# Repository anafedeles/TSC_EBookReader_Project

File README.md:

# TSC_EBookReader_Project

## 
Proiectul **EOpenBook** este o platformă portabilă cu afișaj E-Paper, construită în jurul microcontrollerului ESP32-C6, cu scopul de a oferi o interfață de citire eficientă energetic și complet conectată. Include funcționalități precum:

- Afișare E-Paper cu consum redus
- Stocare locală pe memorie NOR și card microSD
- Monitorizare baterie și încărcare
- Ceas în timp real (RTC)
- Senzor de mediu cu detecție VOC
- Protecții ESD și rutare optimizată

## Diagramă bloc cu toate componentele proiectului

## Listă de materiale (BOM)

| Componentă             | Link pentru achizitionare                                                                                             | Link Datasheet                                                                                                      |
|------------------------|----------------------------------------------------------------------------------------------------------------|---------------------------------------------------------------------------------------------------------------------|
| 112A-TAAR-R03 ATTEND   | https://store.comet.srl.ro/Catalogue/Product/43497/                                                            | https://www.snapeda.com/parts/112A-TAAR-R03/Attend/datasheet/                                                     |
| BD5229G-TR             | https://www.digikey.com/en/products/detail/rohm-semiconductor/BD5229G-TR/3663792                             | https://fscdn.rohm.com/en/products/databook/datasheet/ic/power/voltage_detector/bd52xxg-e.pdf                      |
| ESP32 WROVER BME680 Sensor                 | https://store.comet.srl.ro/Catalogue/Product/50164/             | https://www.bosch-sensortec.com/media/boschsensortec/downloads/datasheets/bst-bme680-ds001.pdf                                                  |
| LED CHG_LED                | https://ro.mouser.com/ProductDetail/Kingbright/KP-1608SURCK?qs=2JU0tDl2GZ3FuyEWfBV1%2Fg==                     | https://www.snapeda.com/parts/KP-1608SURCK/Kingbright/datasheet/                                                  |
| Condensator C0402      | https://ro.mouser.com/c/passive-components/capacitors/ceramic-capacitors/?q=CC0402                           | https://componentsearchengine.com/Datasheets/2/CC0402MRX5R5BB106.pdf                                               |
| Condensator Tant  | https://ro.mouser.com/ProductDetail/KYOCERA-AVX/TAJW107M010RNJ?qs=Wtp%252Bf%2FAeVqIH8v1VxV%252B1Rg%3D%3D        | https://ro.mouser.com/datasheet/2/40/TAJ-3165264.pdf                                                               |
|Q1 DMG2305UX-7            | https://www.digikey.com/en/products/detail/diodes-incorporated/DMG2305UX-7/4340666                           | https://www.diodes.com/assets/Datasheets/DMG2305UX.pdf                                                             |
| RTC MODULE DS3231SN#              | https://www.snapeda.com/parts/DS3231SN%23/Analog+Devices/view-part/?ref=eda | https://www.snapeda.com/parts/DS3231SN%23/Analog%20Devices/datasheet/                                                          |
| ESP32 C6 WROOM-1-N8    | https://ro.mouser.com/ProductDetail/Espressif-Systems/ESP32-C6-WROOM-1-N8?qs=8Wlm6%252BaMh8ST02Gmwp74cw%3D%3D | https://www.snapeda.com/parts/ESP32-C6-WROOM-1-N8/Espressif%20Systems/datasheet/             |
| FH34SRJ-24S-0.5SH(99)  | https://ro.mouser.com/ProductDetail/Hirose-Connector/FH34SRJ-24S-0.5SH99?qs=vcbW%252B4%252BSTIpKBl5ap9J8Fw%3D%3D | https://www.snapeda.com/parts/FH34SRJ-24S-0.5SH(99)/Hirose%20Connector/datasheet/           |
| MAX 17048G+T10          | https://www.snapeda.com/parts/MAX17048G+T10/Analog+Devices/view-part/?ref=eda  | https://www.snapeda.com/parts/MAX17048G+T10/Analog%20Devices/datasheet/                                     |
| MBR0530 Schottky Diode              | https://www.snapeda.com/parts/MBR0530/Onsemi/view-part/?ref=snap            | https://www.snapeda.com/parts/MBR0530/ON%20Semiconductor/datasheet/                                                    |
| ESP32 WROVER MCP73831 Power Management              | ]https://www.snapeda.com/parts/BME680/Bosch/view-part/?welcome=home | https://www.snapeda.com/parts/MCP73831T-2ACI/OT/Microchip/datasheet/                      |
| PFMF.050.1             | https://ro.mouser.com/ProductDetail/EPCOS-TDK/B72520T0350K062?qs=dEfas%2FXlABIszF52uu7vrg%3D%3D               | https://www.tdk-electronics.tdk.com/inf/75/db/CTVS_14/Surge_protection_series.pdf                                  |
| PGB1010603MR           | https://www.snapeda.com/parts/PGB1010603MR/Littelfuse/view-part/?ref=eda                           | https://www.snapeda.com/parts/PGB1010603MR/Littelfuse%20Inc./datasheet/ |
| QWIIC_RIGHT_ANGLE CONNECTOR     | https://ro.mouser.com/ProductDetail/SparkFun/PRT-14417?qs=wd5RIQLrsJhgdz%2FpmZ%2F3GQ==                        | https://ro.mouser.com/datasheet/2/813/Qwiic_Connector_Datasheet-1223982.pdf                                        |
| Rezistență R0402       | https://grabcad.com/library/resistor-0402-1)  | https://www.yageo.com/upload/media/product/products/datasheet/rchip/PYu-RC_Group_51_RoHS_L_12.pdf                 |
| SD0805S020S1R0         | https://ro.mouser.com/ProductDetail/KYOCERA-AVX/SD0805S020S1R0?qs=jCA%252BPfw4LHbpkAoSnwrdjw%3D%3D            | https://ro.mouser.com/datasheet/2/40/schottky-3165252.pdf                                                          |
| Si1308EDL-T1-GE3 MOSFET      | https://www.snapeda.com/parts/SI1308EDL-T1-GE3/Vishay+Siliconix/view-part/?welcome=home&ref=eda                                | https://www.snapeda.com/parts/SI1308EDL-T1-GE3/Vishay%20Siliconix/datasheet/                                                                     |
| USB4110-GF-A           | https://ro.mouser.com/ProductDetail/GCT/USB4110-GF-A?qs=KUoIvG%2F9IlYiZvIXQjyJeA%3D%3D                        | https://ro.mouser.com/datasheet/2/837/GCT_USB4110_Product_Drawing___20k_cycles-3455479.pdf                         |
| USBLC6-2SC6Y           | https://ro.mouser.com/ProductDetail/STMicroelectronics/USBLC6-2SC6Y?qs=gNDSiZmRJS%2FOgDexvXkdow%3D%3D         | https://ro.mouser.com/datasheet/2/389/usblc6_2sc6y-1852505.pdf                                                     |
| W25Q512JVEIQ           | ]https://www.snapeda.com/parts/W25Q512JVEIQ/Winbond+Electronics/view-part/?ref=eda)                     | https://www.winbond.com/resource-files/W25Q512JV%20SPI%20RevB%2006252019%20KMS.pdf)                                      |
| XC6220A331MR-G         | https://componentsearchengine.com/part-view/XC6220A331MR-G/Torex         | https://product.torexsemi.com/system/files/series/xc6220.pdf                                                          |
| 744043680   BOBINA  | https://ro.mouser.com/ProductDetail/Wurth-Elektronik/744043680?qs=PGXP4M47uW6VkZq%252BkzjrHA%3D%3D             | https://www.we-online.com/components/products/datasheet/744043680.pdf                                              |

## Funcționalitatea Hardware 
ESP32-C6 este nucleul EOpenBook-ului, oferind conectivitate Wi-Fi 6 și Bluetooth 5.0 LE. Acesta include:

### Procesor RISC-V single-core de 160MHz
512KB de SRAM
8MB de memorie flash externă
Conectivitate wireless integrată
Multiple pini GPIO pentru interfațarea cu componente periferice

### Afișaj E-Paper

Afișajul e-paper oferă o interfață vizuală cu consum redus pentru EBook
Conectat prin interfața SPI la ESP32-C6
Utilizează driver-ul BD5229G-TR pentru a gestiona diversele tensiuni necesare afișajului
Alimentarea afișajului este controlată de MOSFET-uri pentru a asigura oprirea completă când nu este utilizat
Conectorul afișajului (FH34SRJ-24S-0.5SH) oferă o conexiune fiabilă la modulul flexibil de afișare

### Senzor de Mediu

Senzorul BME688 oferă măsurători pentru:

Temperatură (precizie ±0.5°C)
Umiditate (precizie ±3% RH)
Presiune (precizie ±0.12 hPa)
Calitatea aerului (detectare VOC)
Conectat prin interfața I²C (SCL/SDA)
Funcționează la 3.3V cu un consum tipic de curent de 3.7mA în timpul măsurătorilor

### Gestionarea Energiei

Conector USB-C (112A-TAAR-R03) pentru alimentare și comunicare de date
USBLC6-2SC6Y oferă protecție ESD pentru liniile USB
MCP73831 controller pentru încărcarea bateriei Li-Ion/Li-Polymer cu o singură celulă:

Curent de încărcare programabil până la 500mA
Terminare automată a încărcării
Indicare status prin LED

MAX17048G+T10 monitorizează starea bateriei:

Oferă o estimare precisă a stării de încărcare (SoC)
Comunică prin I²C
Consum redus de energie (23μA)

XC6220A331MR-G LDO oferă o ieșire stabilă de 3.3V:

Interval de tensiune de intrare: 2.0V până la 6.0V
Curent de ieșire până la 700mA
Tensiune de dropout scăzută (90mV tipic la 100mA)

### Ceas în Timp Real

DS3231SN RTC de înaltă precizie:

Oscilator cu cristal compensat în temperatură (TCXO)
Precizie ±2ppm (±1 minut pe an)
Baterie de backup folosind un supercondensator
Interfață I²C pentru comunicare
Funcții de alarmă cu capacitate de întrerupere

### Stocare Externă

W25Q512JVEIQ 512Mb (64MB) Flash NOR Serial:

Interfață SPI la până la 133MHz
100.000 de cicluri de programare/ștergere
Retenție date: 20 de ani
Folosit pentru stocarea datelor aplicației, configurare și actualizări firmware

Interfață card SD pentru stocare extensibilă:

Conectată prin interfață SPI
Suportă formate standard de card SD

### Protecție ESD

Diodele PGB1010603MR protejează liniile SPI sensibile
USBLC6-2SC6Y protejează liniile de date USB
Layout-ul atent al PCB-ului cu planuri de masă și rutare corespunzătoare îmbunătățește performanța EMI/EMC

### Analiza Consumului de Energie

Mod de repaus: <50μA (ESP32-C6 în deep sleep, RTC activ)
Mod inactiv: ~25mA (ESP32-C6 treaz, periferice în standby)
Mod activ: ~150mA (toate sistemele active, fără a include reîmprospătarea afișajului)
Reîmprospătare afișaj: ~20mA vârf în timpul reîmprospătării, 0mA când este static
Estimare durată de viață a bateriei:

Cu o baterie tipică LiPo de 2000mAh
~80 de ore de funcționare continuă în mod inactiv
~2-3 săptămâni cu modele tipice de utilizare (treziri periodice și actualizări ale afișajului)

## Alocarea Pinilor ESP32-C6

| Componentă                 | Pini ESP32-C6 (funcție)                                                  | Note / Utilizare                                                                 |
|---------------------------|--------------------------------------------------------------------------|-----------------------------------------------------------------------------------|
| **E-Paper Display**       | IO3 (EPD_BUSY), IO5 (EPD_DC), IO6 (SCK), IO7 (MOSI), IO10 (EPD_CS), IO23 (EPD_RST), IO20 (EPD_3V3_C) | Interfață SPI; include semnalizare BUSY și control reset/alimentare               |
| **Magistrala I2C**        | IO21 (SDA), IO22 (SCL), IO19 (I2C_PW)                                     | Comun pentru BME688, MAX17048, DS3231; I2C_PW pentru control alimentare senzori  |
| **RTC DS3231SN**          | IO0 (INT_RTC), IO1 (32KHz), IO18 (RTC_RST)                                | Întrerupere externă, semnal 32KHz opțional, reset hardware                        |
| **USB**                   | IO12 (USB_D-), IO13 (USB_D+)                                              | Comunicație USB cu PC                                                             |
| **UART**                  | IO16 (TX), IO17 (RX)                                                      | Comunicație serială pentru programare/debug                                       |
| **Card SD**               | IO2 (MISO), IO4 (SS_SD), IO6 (SCK), IO7 (MOSI)                            | SPI partajat; CS dedicat pentru card SD                                           |
| **Memorie Flash NOR**     | IO11 (FLASH_CS), IO2 (MISO), IO6 (SCK), IO7 (MOSI)                        | Partajează SPI cu SD și EPD; CS dedicat                                           |
| **Butoane**               | EN (RESET), IO8 (IO/BOOT), IO15 (IO/CHANGE)                               | BOOT pentru mod programare; CHANGE pentru acțiuni personalizate                   |
| **Alimentare & GND**      | Pin 2 (3V3), Pin 1 (GND)                                                  | Alimentare stabilă 3.3V; masă comună                                              |

Bus SPI: Bus-ul SPI este partajat între mai multe dispozitive (afișaj, flash, card SD) pentru a minimiza utilizarea pinilor. Fiecare dispozitiv are un pin dedicat de selectare a chip-ului pentru a asigura o comunicare corectă.
Bus I2C: Un singur bus I2C conectează toate dispozitivele I2C (BME688, RTC, indicator baterie) pentru a minimiza utilizarea pinilor, oferind în același timp o comunicare fiabilă la viteze standard (100kHz-400kHz).
Pini GPIO: Pinii cu capacitate de întrerupere (IO13, IO19) au fost selectați pentru funcții care necesită funcționalitate de trezire.
UART: Pinii standard UART (IO16/IO17) sunt utilizați pentru programare și depanare pentru a asigura compatibilitatea cu instrumentele standard de dezvoltare.
Gestionarea Energiei: Pinii de control pentru domeniile de alimentare sunt configurați pentru a permite controlul individual al perifericelor pentru o gestionare optimă a energiei.

## Detalii Suplimentare de Proiectare

Pentru a preveni eventualele erori la nivelul plăcii PCB, am ajustat dimensiunile anumitor footprint-uri și am corectat pad-urile, astfel încât să respecte normele de funcționare corespunzătoare. De asemenea, am aplicat regulile din checklist-ul de proiectare, inclusiv poziționarea condensatorilor de decuplare cât mai aproape de pinii VCC ai circuitelor integrate.
### Asezarea TP-urilor: 
TP-urile au fost amplasate strategic în apropierea marginilor plăcii de circuit imprimat și în vecinătatea componentelor cheie. Această alegere facilitează accesul pentru operațiunile de depanare și testare.
### Diode (Montare pe Suprafață ):
Designul inițial al amprentei pentru diode prezenta orificii de contact (pad holes) cu un diametru insuficient, ceea ce ar fi putut genera dificultăți semnificative în procesul de lipire. Pentru a asigura o fabricație fără probleme și o conexiune electrică solidă, dimensiunea acestor orificii a fost revizuită.
### Rutare și Plan de Masă: 
Rutarea traseelor a fost realizată atât pe stratul superior, cât și pe stratul inferior al PCB-ului. Această strategie a necesitat utilizarea unui total de 105 vias pentru a interconecta diferitele straturi și a permite o rutare complexă a semnalelor. Deși un număr mare de vias poate influența costul și complexitatea fabricației, utilizarea ambelor straturi oferă o flexibilitate sporită în distribuția semnalelor și a alimentării. Planul de masă (GND) a fost implementat după finalizarea rutării, fiind aplicat pe ambele straturi ale plăcii (superior și inferior). 
În realizarea designului am urmărit respectarea riguroasă a regulilor impuse de ERC și DRC. Amplasarea componentelor a fost realizată pe baza documentației tehnice disponibile (dimensiuni și recomandări de plasare), dar și ținând cont de cerințele de rutare și de asigurarea unei funcționări optime a dispozitivului.

## Concluzie

Designul hardware al proiectului **EOpenBook** îmbină performanța, eficiența energetică și modularitatea. Fiecare componentă a fost atent aleasă și integrată cu respectarea standardelor de proiectare (ERC/DRC). PCB-ul rezultat este pregătit pentru fabricație și testare, având o structură robustă, consum redus și compatibilitate excelentă cu cerințele mecanice.

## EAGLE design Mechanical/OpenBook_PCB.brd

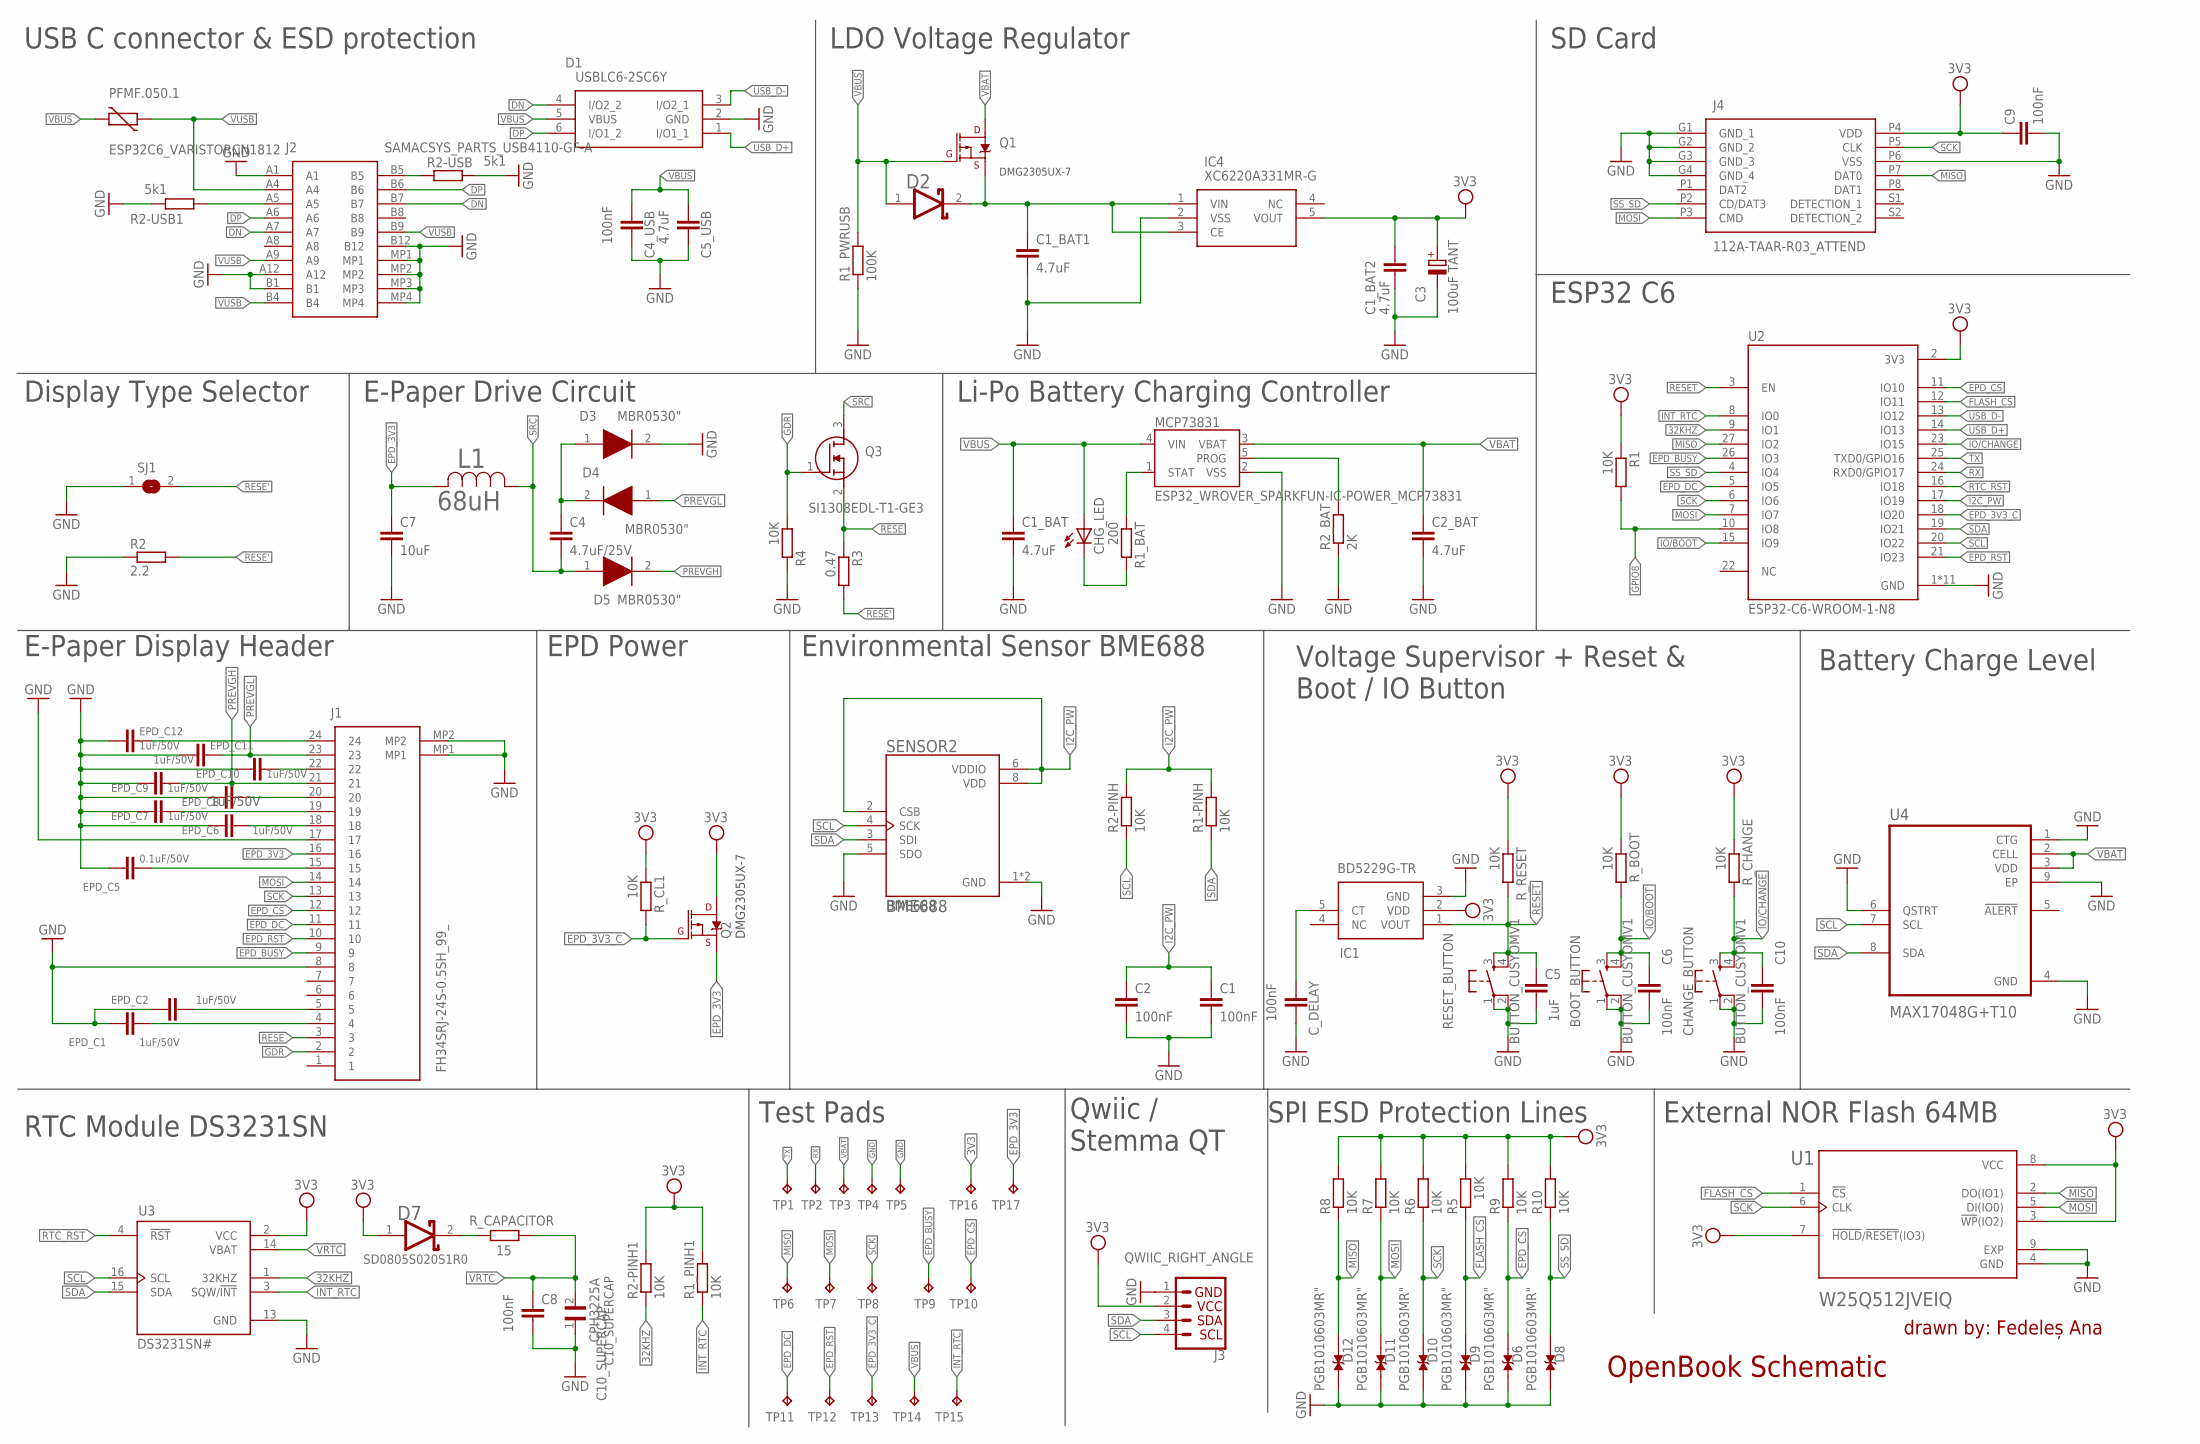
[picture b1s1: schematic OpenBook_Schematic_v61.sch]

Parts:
BOOT_BUTTON: BUTTON_CUSYOMV1; MYBUTTON
C1, C2, C4_USB, C6, C8, C9, C10: 100nF; ESP32_WROVER_EAGLE-LTSPICE_C0402
C1_BAT, C1_BAT1, C1_BAT2, C2_BAT, C5_USB: 4.7uF; ESP32_WROVER_EAGLE-LTSPICE_C0402
C3: 100uF TANT; RCL_CT3528
C4: 4.7uF/25V; ESP32_WROVER_EAGLE-LTSPICE_C0402
C5: 1uF; ESP32_WROVER_EAGLE-LTSPICE_C0402
C7: 10uF; ESP32_WROVER_EAGLE-LTSPICE_C0402
C10_SUPERCAP: CPH3225A; CAPCP3225X100N
CHANGE_BUTTON: BUTTON_CUSYOMV1; MYBUTTON
CHG_LED: ADAFRUIT_LEDCHIP-LED0603; ADAFRUIT_CHIP-LED0603
C_DELAY: 100nF; ESP32_WROVER_EAGLE-LTSPICE_C0402
D1: USBLC6-2SC6Y; SOT95P280X145-6N
D2: ESP32_WROVER_AVX---SD0805S020S1R0_AVX_SD0805S020S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; ESP32_WROVER_AVX---SD0805S020S1R0_AVX_SD0805S020S1R0_0
D3, D4, D5: MBR0530"; SOD3716X135N
D6, D8, D9, D10, D11, D12: PGB1010603MR"; DIOC1608X36N
D7: SD0805S020S1R0; ESP32_WROVER_AVX---SD0805S020S1R0_AVX_SD0805S020S1R0_0
EPD_C1, EPD_C2, EPD_C6, EPD_C7, EPD_C8, EPD_C9, EPD_C10, EPD_C11, EPD_C12: 1uF/50V; ESP32_WROVER_EAGLE-LTSPICE_C0402
EPD_C5: 0.1uF/50V; ESP32_WROVER_EAGLE-LTSPICE_C0402
IC1: BD5229G-TR; SOT95P280X125-5N
IC4: XC6220A331MR-G; SOT95P280X120-5N
J1: FH34SRJ-24S-0.5SH_99_; FH34SRJ24S05SH99
J2: SAMACSYS_PARTS_USB4110-GF-A; SAMACSYS_PARTS_USB4110GFA
J3: QWIIC_RIGHT_ANGLE; JST04_1MM_RA
J4: 112A-TAAR-R03_ATTEND; 112ATAARR03ATTEND
L1: 68uH; IND_4828-WE-TPC_WRE
MCP73831: ESP32_WROVER_SPARKFUN-IC-POWER_MCP73831; ESP32_WROVER_SPARKFUN-IC-POWER_SOT23-5
PFMF.050.1: ESP32C6_VARISTORCN1812; ESP32C6_VARISTOR_CT/CN1812
Q1, Q2: 20V/4.2A/52mΩ/1.4W; ESP32_WROVER_SPARKFUN-DISCRETESEMI_SOT23-3
Q3: SI1308EDL-T1-GE3; SOT65P210X110-3N
R1, R1-PINH, R1_PINH1, R2-PINH, R2-PINH1, R4, R5, R6, R7, R8, R9, R10: 10K; ESP32_WROVER_EAGLE-LTSPICE_R0402
R1_BAT: 200; ESP32_WROVER_EAGLE-LTSPICE_R0402
R1_PWRUSB: 100K; ESP32_WROVER_EAGLE-LTSPICE_R0402
R2: 2.2; ESP32_WROVER_EAGLE-LTSPICE_R0402
R2-USB, R2-USB1: 5k1; ESP32_WROVER_EAGLE-LTSPICE_R0402
R2_BAT: 2K; ESP32_WROVER_EAGLE-LTSPICE_R0402
R3: 0.47; ESP32_WROVER_EAGLE-LTSPICE_R0402
RESET_BUTTON: BUTTON_CUSYOMV1; MYBUTTON
R_BOOT: 10K; ESP32_WROVER_EAGLE-LTSPICE_R0402
R_CAPACITOR: 15; ESP32_WROVER_EAGLE-LTSPICE_R0402
R_CHANGE: 10K; ESP32_WROVER_EAGLE-LTSPICE_R0402
R_CL1: 10K; ESP32_WROVER_EAGLE-LTSPICE_R0402
R_RESET: 10K; ESP32_WROVER_EAGLE-LTSPICE_R0402
SENSOR2: BME688; ESP32_WROVER_BME680_PSON80P300X300X100-8N
SJ1: SJ
TP1, TP2, TP3, TP4, TP5, TP6, TP7, TP8, TP9, TP10, TP11, TP12, TP13, TP14, TP15, TP16, TP17: TPTP20R; TP20R
U1: W25Q512JVEIQ; SON127P600X800X80-9N
U2: ESP32-C6-WROOM-1-N8; XCVR_ESP32-C6-WROOM-1-N8
U3: DS3231SN#; SOIC127P1032X265-16N
U4: MAX17048G+T10; SON50P200X200X80-9N

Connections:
3V3: C1_BAT2.1, C3.+, C9.1, D7.1 (ANODE), IC1.2 (VDD), IC4.5 (VOUT), J3.2, J4.P4 (VDD), Q2.1 (D), R1.1, R1_PINH1.2, R2-PINH1.2, R5.2, R6.2, R7.2, R8.2, R9.2, R10.2, R_BOOT.1, R_CHANGE.1, R_CL1.1, R_RESET.1, TP16.TP, U1.3 (!WP!(IO2)), U1.7 (!HOLD!/!RESET!(IO3)), U1.8 (VCC), U2.2 (3V3), U3.2 (VCC)
32KHZ: R2-PINH1.1, U2.9 (IO1), U3.1 (32KHZ)
DN: D1.4 (I/O2_2), J2.A7, J2.B7
DP: D1.6 (I/O1_2), J2.A6, J2.B6
EPD_3V3: C7.1, J1.16, L1.2, Q2.3 (S), TP17.TP
EPD_3V3_C: Q2.2 (G), R_CL1.2, TP13.TP, U2.18 (IO20)
EPD_BUSY: J1.9, TP9.TP, U2.26 (IO3)
EPD_CS: D6.2, J1.12, R9.1, TP10.TP, U2.11 (IO10)
EPD_DC: J1.11, TP11.TP, U2.5 (IO5)
EPD_RST: J1.10, TP12.TP, U2.21 (IO23)
FLASH_CS: D9.2, R5.1, U1.1 (!CS), U2.12 (IO11)
GDR: J1.2, Q3.1 (G), R4.1
GND: BOOT_BUTTON.1, BOOT_BUTTON.2, C1.2, C1_BAT.2, C1_BAT1.2, C1_BAT2.2, C2.2, C2_BAT.2, C3.-, C4_USB.2, C5.2, C5_USB.2, C6.2, C7.2, C8.2, C9.2, C10.2, C10_SUPERCAP.1, CHANGE_BUTTON.1, CHANGE_BUTTON.2, C_DELAY.2, D1.2 (GND), D3.2 (K), D6.1, D8.1, D9.1, D10.1, D11.1, D12.1, EPD_C1.2, EPD_C2.2, EPD_C5.2, EPD_C6.2, EPD_C7.2, EPD_C8.2, EPD_C9.2, EPD_C10.2, EPD_C11.2, EPD_C12.2, IC1.3 (GND), IC4.2 (VSS), J1.8, J1.17, J1.MP1, J1.MP2, J2.A1, J2.A12, J2.B1, J2.B12, J2.MP1, J2.MP2, J2.MP3, J2.MP4, J3.1, J4.G1 (GND_1), J4.G2 (GND_2), J4.G3 (GND_3), J4.G4 (GND_4), J4.P6 (VSS), MCP73831.2 (VSS), R1_PWRUSB.1, R2.1, R2-USB.2, R2-USB1.1, R2_BAT.1, R4.2, RESET_BUTTON.1, RESET_BUTTON.2, SENSOR2.1 (GND), SENSOR2.5 (SDO), SENSOR2.7 (GND), SJ1.1, TP4.TP, TP5.TP, U1.4 (GND), U1.9 (EXP), U2.1 (GND), U2.28 (GND), U2.29_1 (GND), U2.29_2 (GND), U2.29_3 (GND), U2.29_4 (GND), U2.29_5 (GND), U2.29_6 (GND), U2.29_7 (GND), U2.29_8 (GND), U2.29_9 (GND), U3.13 (GND), U4.1 (CTG), U4.4 (GND), U4.6 (QSTRT), U4.9 (EP)
GPIO8: R1.2, U2.10 (IO8)
I2C_PW: C1.1, C2.1, R1-PINH.2, R2-PINH.2, SENSOR2.2 (CSB), SENSOR2.6 (VDDIO), SENSOR2.8 (VDD), U2.17 (IO19)
INT_RTC: R1_PINH1.1, TP15.TP, U2.8 (IO0), U3.3 (SQW/!INT)
IO/BOOT: BOOT_BUTTON.3, BOOT_BUTTON.4, C6.1, R_BOOT.2, U2.15 (IO9)
IO/CHANGE: C10.1, CHANGE_BUTTON.3, CHANGE_BUTTON.4, R_CHANGE.2, U2.23 (IO15)
MISO: D12.2, J4.P7 (DAT0), R8.1, TP6.TP, U1.2 (DO(IO1)), U2.27 (IO2)
MOSI: D11.2, J1.14, J4.P3 (CMD), R7.1, TP7.TP, U1.5 (DI(IO0)), U2.7 (IO7)
unnamed: J2.A5, R2-USB1.2
unnamed: J2.B5, R2-USB.1
unnamed: MCP73831.1 (STAT), R1_BAT.1
unnamed: C1_BAT1.1, D2.2 (CATHODE), IC4.1 (VIN), IC4.3 (CE), Q1.3 (S)
unnamed: CHG_LED.C, R1_BAT.2
unnamed: EPD_C6.1, J1.18
unnamed: C_DELAY.1, IC1.5 (CT)
unnamed: C4.1, D3.1 (A), D4.2 (K)
unnamed: MCP73831.5 (PROG), R2_BAT.2
unnamed: EPD_C1.1, J1.4
unnamed: EPD_C2.1, J1.5
unnamed: EPD_C5.1, J1.15
unnamed: EPD_C8.1, J1.20
unnamed: EPD_C7.1, J1.19
unnamed: EPD_C10.1, J1.22
unnamed: EPD_C12.1, J1.24
unnamed: D7.2 (CATHODE), R_CAPACITOR.2
PREVGH: D5.2 (K), EPD_C9.1, J1.21
PREVGL: D4.1 (A), EPD_C11.1, J1.23
RESE: J1.3, Q3.2 (S), R3.1
RESE': R2.2, R3.2, SJ1.2
RESET: C5.1, IC1.1 (VOUT), RESET_BUTTON.3, RESET_BUTTON.4, R_RESET.2, U2.3 (EN)
RTC_RST: U2.16 (IO18), U3.4 (!RST)
RX: TP2.TP, U2.24 (RXD0/GPIO17)
SCK: D10.2, J1.13, J4.P5 (CLK), R6.1, TP8.TP, U1.6 (CLK), U2.6 (IO6)
SCL: J3.4, R2-PINH.1, SENSOR2.4 (SCK), U2.20 (IO22), U3.16 (SCL), U4.7 (SCL)
SDA: J3.3, R1-PINH.1, SENSOR2.3 (SDI), U2.19 (IO21), U3.15 (SDA), U4.8 (SDA)
SRC: C4.2, D5.1 (A), L1.1, Q3.3 (D)
SS_SD: D8.2, J4.P2 (CD/DAT3), R10.1, U2.4 (IO4)
TX: TP1.TP, U2.25 (TXD0/GPIO16)
USB_D+: D1.1 (I/O1_1), U2.14 (IO13)
USB_D-: D1.3 (I/O2_1), U2.13 (IO12)
VBAT: C2_BAT.1, MCP73831.3 (VBAT), Q1.1 (D), TP3.TP, U4.2 (CELL), U4.3 (VDD)
VBUS: C1_BAT.1, C4_USB.1, C5_USB.1, CHG_LED.A, D1.5 (VBUS), D2.1 (ANODE), MCP73831.4 (VIN), PFMF.050.1.2, Q1.2 (G), R1_PWRUSB.2, TP14.TP
VRTC: C8.1, C10_SUPERCAP.2, R_CAPACITOR.1, U3.14 (VBAT)
VUSB: J2.A4, J2.A9, J2.B4, J2.B9, PFMF.050.1.1

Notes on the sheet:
BME688
USB C connector & ESD protection
DMG2305UX-7
LDO Voltage Regulator
SD Card
Display Type Selector
E-Paper Drive Circuit
Li-Po Battery Charging Controller
ESP32 C6
E-Paper Display Header
EPD Power
Environmental Sensor BME688
Voltage Supervisor + Reset & Boot / IO Button
Battery Charge Level
SD0805S020S1R0
RTC Module DS3231SN
Test Pads
Qwiic / Stemma QT
SPI ESD Protection Lines
External NOR Flash 64MB
OpenBook Schematic
drawn by: Fedeleș Ana
C10_SUPERCAP

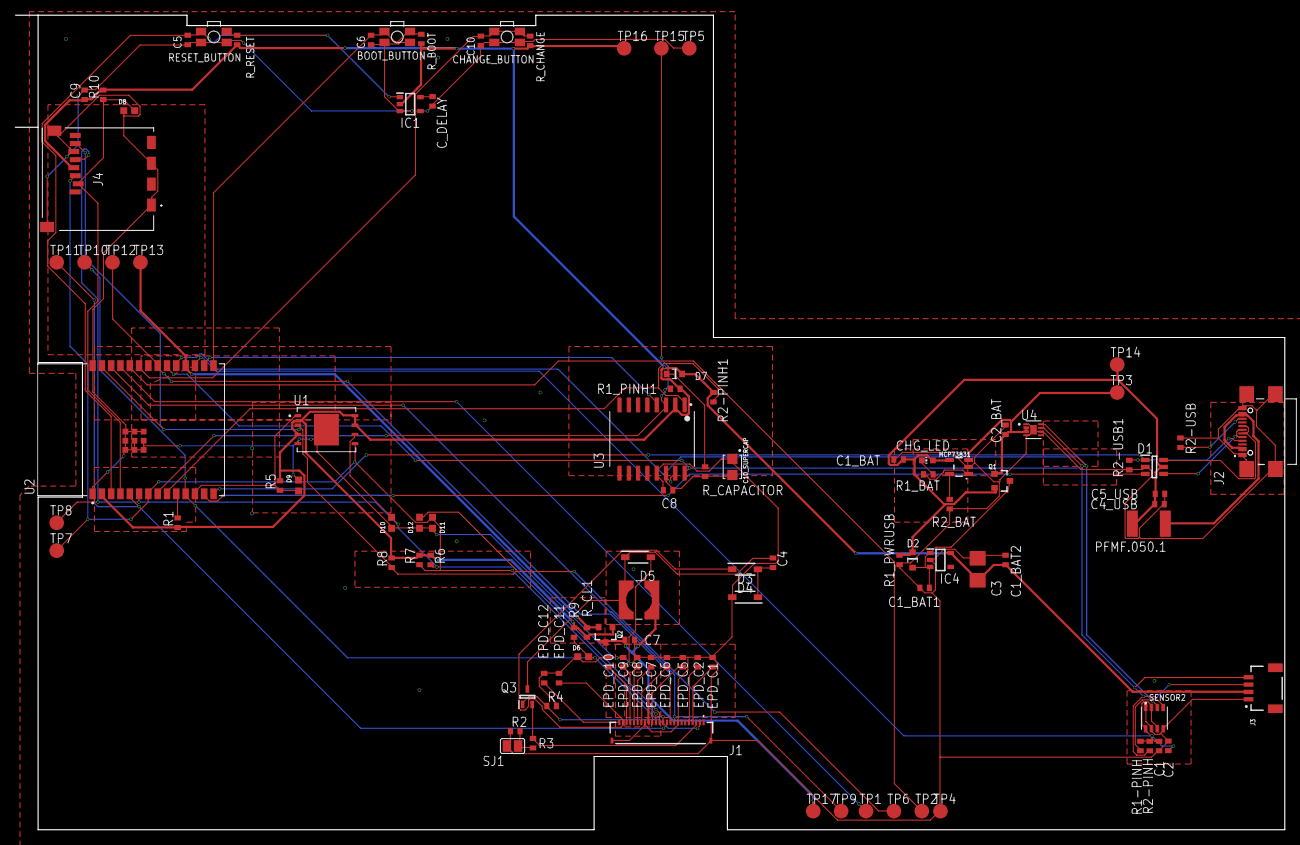
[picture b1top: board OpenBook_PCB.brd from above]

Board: 2 copper layers, 173.3 x 111.2 mm, 103 parts (0 on the bottom side), 56 nets.

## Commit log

2025-04-06 Create Hardware
2025-04-06 Rename Hardware to Hardwareee
2025-04-06 Hardware files uploaded
2025-04-06 Manufacturing files commited
2025-04-06 Create LICENSE
2025-04-14 Commit improved Images done
2025-04-14 Better 3D Implementation Done
2025-04-14 Better Organization Mechnical Folder done
2025-04-14 Improved PCB- commit done
2025-04-14 Revert "Better 3D Implementation Done"
2025-04-14 Better Mechanical Folder organization- done
2025-04-15 exploded view done

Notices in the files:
parts and their libraries:
DeskAssistant v19 v1: COPYRIGHT: Copyright (C) 2024 Ultra Librarian. All rights reserved.
